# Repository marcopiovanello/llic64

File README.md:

Yet-Another-ControlPort-Converter for the Commodore C64

WIP!!

I'm developing yet another converter for Atari joystick based systems to USB.

What's different from other solutions?

Basically it's externally powered, which means that you can plug virtually anything and not think about drawing too much power from the system (e.g. the 100mA limit of the C64)

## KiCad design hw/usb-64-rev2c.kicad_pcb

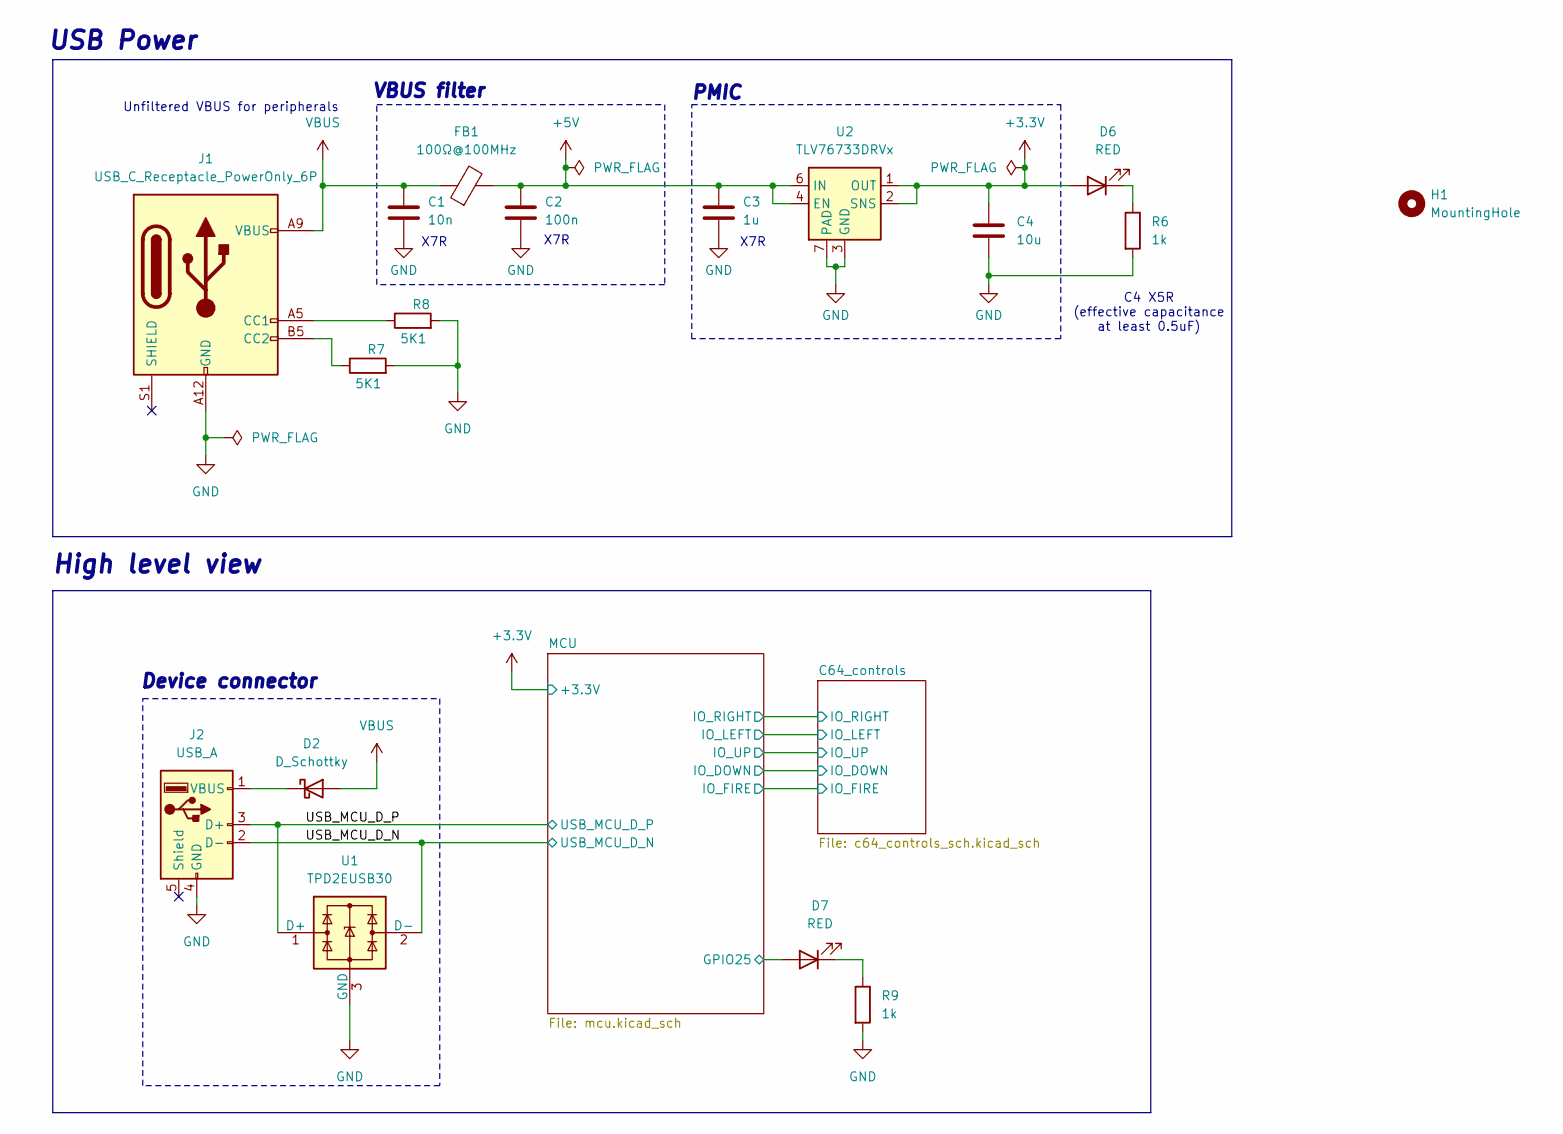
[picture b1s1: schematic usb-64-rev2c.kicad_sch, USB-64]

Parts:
C1: 10n; C_0402_1005Metric; LCSC Part # C15195
C2: 100n; C_0603_1608Metric; LCSC Part # C14663
C3: 1u; C_0603_1608Metric; LCSC Part # C15849
C4: 10u; C_0805_2012Metric; LCSC Part # C440198
D2: D_Schottky; D_SOD-323; LCSC Part # C191023
D6, D7: RED; LED_0603_1608Metric; LCSC Part # C2286
FB1: 100Ω@100MHz; L_0805_2012Metric; LCSC Part # C1015
H1: MountingHole; MountingHole_2.2mm_M2
J1: USB_C_Receptacle_PowerOnly_6P; USB_C_Receptacle_GCT_USB4125-xx-x_6P_TopMnt_Horizontal; LCSC Part # C456012
J2: USB_A; CONN_UJ2-AH-SMT_CUD
R6, R9: 1k; R_0402_1005Metric; LCSC Part # C11702
R7, R8: 5K1; R_0402_1005Metric
U1: TPD2EUSB30; Texas_DRT-3; LCSC Part # C97502
U2: TLV76733DRVx; WSON-6-1EP_2x2mm_P0.65mm_EP1x1.6mm_ThermalVias; LCSC Part # C2848334

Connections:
+3.3V: C4.1, D6.2 (A), U2.1 (OUT), U2.2 (SNS); also elsewhere on the board
+5V: C2.1, C3.1, FB1.2, U2.4 (EN), U2.6 (IN); also elsewhere on the board
/MCU/GPIO25: D7.2 (A); also elsewhere on the board
/USB_MCU_D_N: J2.2 (D-), U1.2 (D-); also elsewhere on the board
/USB_MCU_D_P: J2.3 (D+), U1.1 (D+); also elsewhere on the board
GND: C1.2, C2.2, C3.2, C4.2, J1.A12 (GND), J1.B12 (GND), J2.4 (GND), R6.2, R7.2, R8.2, R9.2, U1.3 (GND), U2.3 (GND), U2.5 (GND), U2.7 (PAD); also elsewhere on the board
unnamed: D2.1 (K), J2.1 (VBUS)
unnamed: D6.1 (K), R6.1
unnamed: D7.1 (K), R9.1
unnamed: J1.A5 (CC1), R8.1
unnamed: J1.B5 (CC2), R7.1
VBUS: C1.1, D2.2 (A), FB1.1, J1.A9 (VBUS), J1.B9 (VBUS)

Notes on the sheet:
PMIC
X7R
USB Power
X7R
High level view
Unfiltered VBUS for peripherals
C4 X5R (effective capacitance at least 0.5uF)
Device connector
VBUS filter

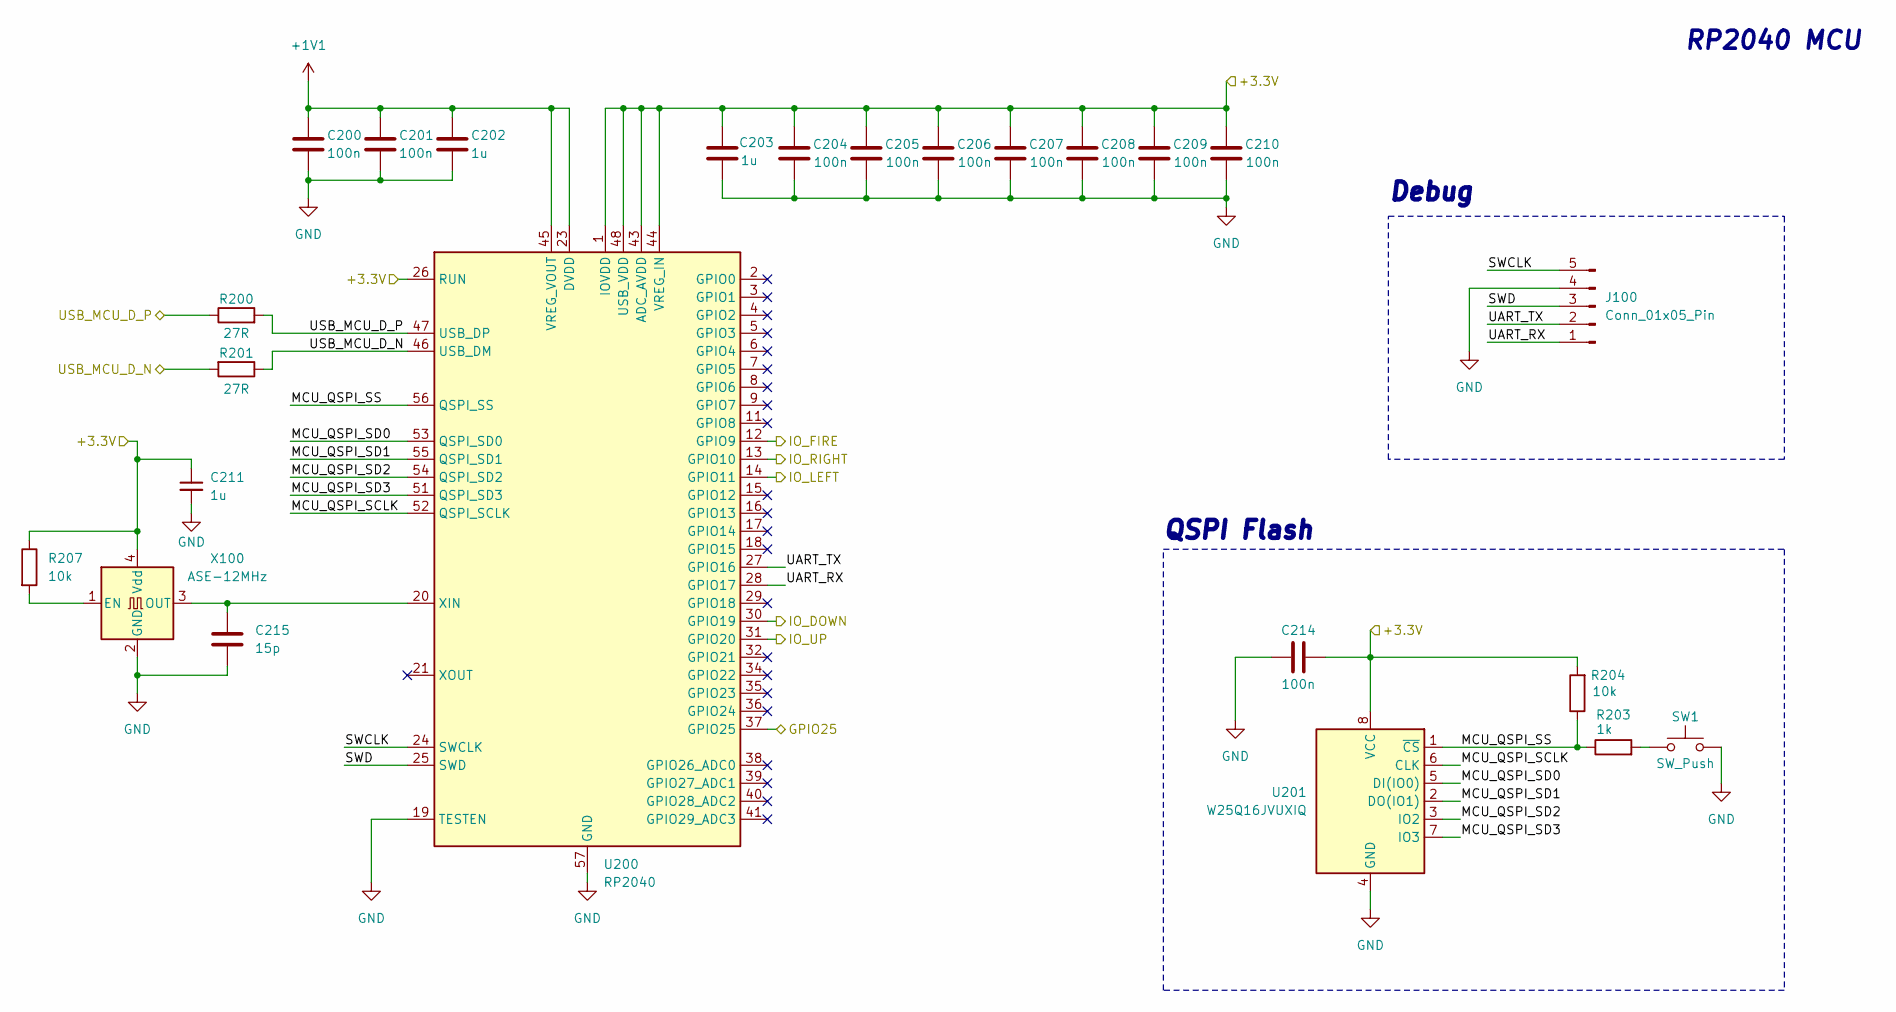
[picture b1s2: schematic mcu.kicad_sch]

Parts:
C200, C201, C204, C205, C206, C207, C208, C209, C210, C214: 100n; C_0402_1005Metric; LCSC Part # C1525
C202, C203, C211: 1u; C_0402_1005Metric; LCSC Part # C52923
C215: 15p; C_0402_1005Metric
J100: Conn_01x05_Pin; PinHeader_1x05_P2.54mm_Vertical
R200, R201: 27R; R_0402_1005Metric; LCSC Part # C25092
R203: 1k; R_0402_1005Metric; LCSC Part # C11702
R204, R207: 10k; R_0402_1005Metric
SW1: SW_Push; SW_SPST_B3U-1000P; LCSC Part # C498294
U200: RP2040; QFN-56-1EP_7x7mm_P0.4mm_EP3.2x3.2mm_ThermalVias
U201: W25Q16JVUXIQ; Winbond_USON-8-1EP_3x2mm_P0.5mm_EP0.2x1.6mm; LCSC Part # C2843335
X100: ASE-12MHz; Crystal_SMD_2016-4Pin_2.0x1.6mm; LCSC Part # C669076

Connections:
+1V1: C200.1, C201.1, C202.1, U200.23 (DVDD), U200.45 (VREG_VOUT), U200.50 (DVDD)
+3.3V: C203.1, C204.1, C205.1, C206.1, C207.1, C208.1, C209.1, C210.1, C211.1, C214.2, R204.2, R207.1, U200.1 (IOVDD), U200.10 (IOVDD), U200.22 (IOVDD), U200.26 (RUN), U200.33 (IOVDD), U200.42 (IOVDD), U200.43 (ADC_AVDD), U200.44 (VREG_IN), U200.48 (USB_VDD), U200.49 (IOVDD), U201.8 (VCC), X100.4 (Vdd); also elsewhere on the board
/C64_controls/IO_DOWN: U200.30 (GPIO19); also elsewhere on the board
/C64_controls/IO_FIRE: U200.12 (GPIO9); also elsewhere on the board
/C64_controls/IO_LEFT: U200.14 (GPIO11); also elsewhere on the board
/C64_controls/IO_RIGHT: U200.13 (GPIO10); also elsewhere on the board
/C64_controls/IO_UP: U200.31 (GPIO20); also elsewhere on the board
/MCU/GPIO25: U200.37 (GPIO25); also elsewhere on the board
/MCU/MCU_QSPI_SCLK: U200.52 (QSPI_SCLK), U201.6 (CLK)
/MCU/MCU_QSPI_SD0: U200.53 (QSPI_SD0), U201.5 (DI(IO0))
/MCU/MCU_QSPI_SD1: U200.55 (QSPI_SD1), U201.2 (DO(IO1))
/MCU/MCU_QSPI_SD2: U200.54 (QSPI_SD2), U201.3 (IO2)
/MCU/MCU_QSPI_SD3: U200.51 (QSPI_SD3), U201.7 (IO3)
/MCU/MCU_QSPI_SS: R203.1, R204.1, U200.56 (QSPI_SS), U201.1 (~CS)
/MCU/SWCLK: J100.5, U200.24 (SWCLK)
/MCU/SWD: J100.3, U200.25 (SWD)
/MCU/UART_RX: J100.1, U200.28 (GPIO17)
/MCU/UART_TX: J100.2, U200.27 (GPIO16)
/USB_MCU_D_N: R201.1, R201.2, U200.46 (USB_DM); also elsewhere on the board
/USB_MCU_D_P: R200.1, R200.2, U200.47 (USB_DP); also elsewhere on the board
GND: C200.2, C201.2, C202.2, C203.2, C204.2, C205.2, C206.2, C207.2, C208.2, C209.2, C210.2, C211.2, C214.1, C215.2, J100.4, SW1.2, U200.19 (TESTEN), U200.57 (GND), U201.4 (GND), X100.2 (GND); also elsewhere on the board
unnamed: R203.2, SW1.1
unnamed: C215.1, U200.20 (XIN), X100.3 (OUT)
unnamed: R207.2, X100.1 (EN)

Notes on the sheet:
Debug
RP2040 MCU
QSPI Flash

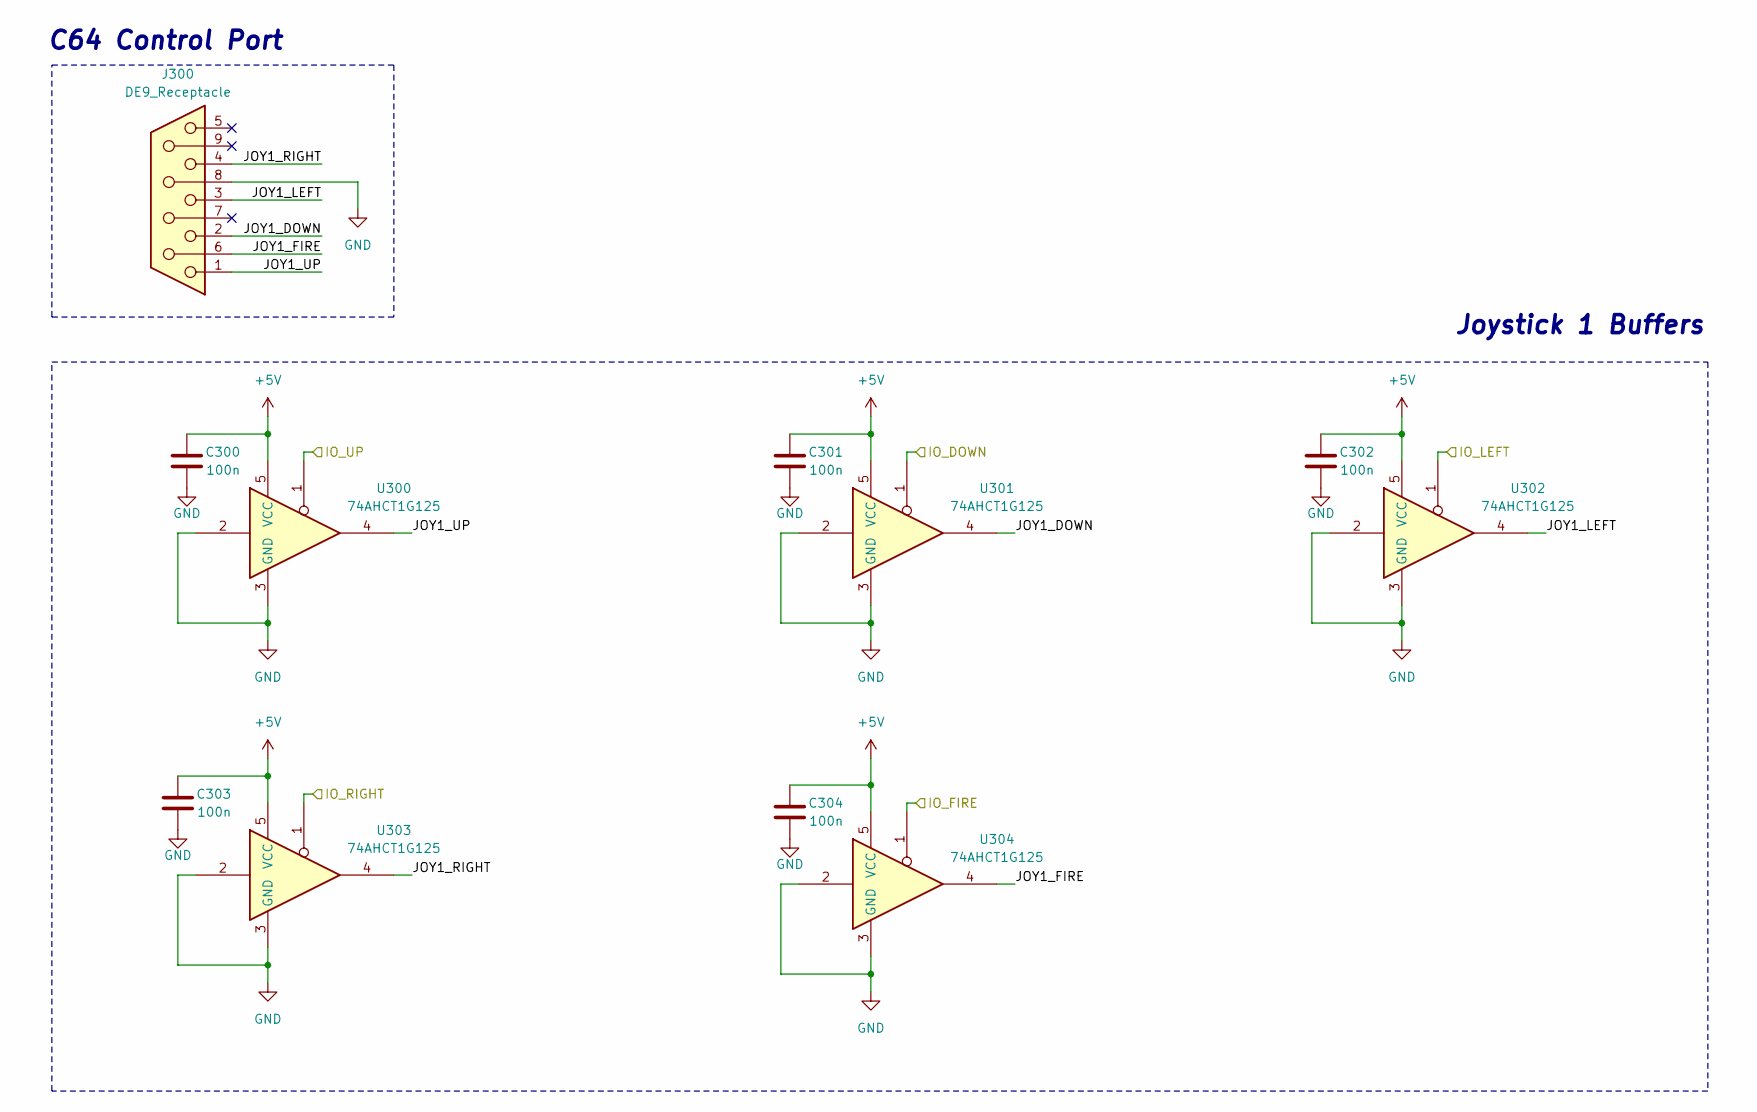
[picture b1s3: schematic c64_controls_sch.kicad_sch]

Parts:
C300, C301, C302, C303, C304: 100n; C_0402_1005Metric; LCSC Part # C1525
J300: DE9_Receptacle; DSUB-9_Female_EdgeMount_P2.77mm
U300, U301, U302, U303, U304: 74AHCT1G125; SOT-353_SC-70-5

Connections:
+5V: C300.1, C301.1, C302.1, C303.1, C304.1, U300.5 (VCC), U301.5 (VCC), U302.5 (VCC), U303.5 (VCC), U304.5 (VCC); also elsewhere on the board
/C64_controls/IO_DOWN: U301.1; also elsewhere on the board
/C64_controls/IO_FIRE: U304.1; also elsewhere on the board
/C64_controls/IO_LEFT: U302.1; also elsewhere on the board
/C64_controls/IO_RIGHT: U303.1; also elsewhere on the board
/C64_controls/IO_UP: U300.1; also elsewhere on the board
/C64_controls/JOY1_DOWN: J300.2, U301.4
/C64_controls/JOY1_FIRE: J300.6, U304.4
/C64_controls/JOY1_LEFT: J300.3, U302.4
/C64_controls/JOY1_RIGHT: J300.4, U303.4
/C64_controls/JOY1_UP: J300.1, U300.4
GND: C300.2, C301.2, C302.2, C303.2, C304.2, J300.8, U300.2, U300.3 (GND), U301.2, U301.3 (GND), U302.2, U302.3 (GND), U303.2, U303.3 (GND), U304.2, U304.3 (GND); also elsewhere on the board

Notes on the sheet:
C64 Control Port
Joystick 1 Buffers

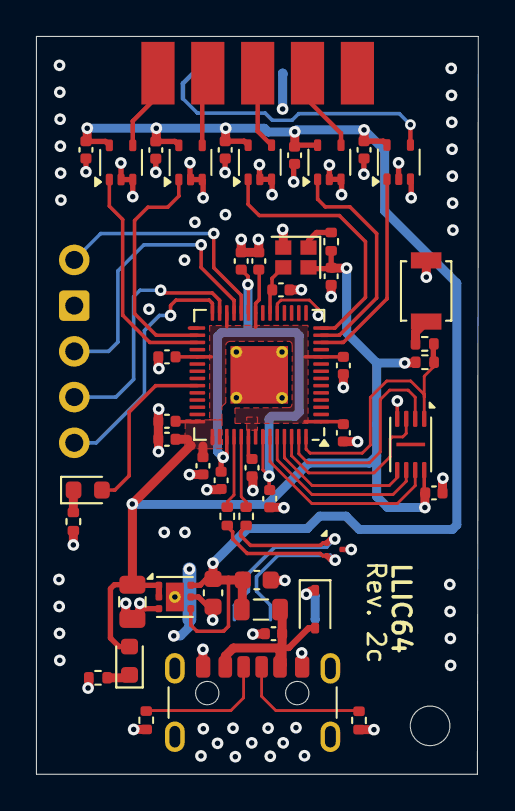
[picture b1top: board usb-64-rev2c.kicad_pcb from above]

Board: 4 copper layers, 24.5 x 41.0 mm, 52 parts (1 on the bottom side), 36 nets.

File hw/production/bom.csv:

Designator,Footprint,Quantity,Value,LCSC Part #
C1,0402,1,10n,C15195
C2,0603,1,100n,C14663
"C200, C201, C204, C205, C206, C207, C208, C209, C210, C214, C300, C301, C302, C303, C304",0402,15,100n,C1525
"C202, C203, C211",0402,3,1u,C52923
C215,0402,1,15p,C1548
C3,0603,1,1u,C15849
C4,0805,1,10u,C440198
D2,D_SOD-323,1,D_Schottky,C191023
"D6, D7",0603,2,RED,C2286
FB1,0805,1,100Ω@100MHz,C1015
J1,USB_C_Receptacle_GCT_USB4125-xx-x_6P_TopMnt_Horizontal,1,USB_C_Receptacle_PowerOnly_6P,C456012
J100,PinHeader_1x05_P2.54mm_Vertical,1,Conn_01x05_Pin,
J2,CONN_UJ2-AH-SMT_CUD,1,USB_A,
J300,DSUB-9_Female_EdgeMount_P2.77mm,1,DE9_Receptacle,
"R200, R201",0402,2,27R,C25092
"R203, R6, R9",0402,3,1k,C11702
"R204, R207",0402,2,10k,
"R7, R8",0402,2,5K1,
SW1,SW_SPST_B3U-1000P,1,SW_Push,C498294
U1,Texas_DRT-3,1,TPD2EUSB30,C97502
U2,WSON-6-1EP_2x2mm_P0.65mm_EP1x1.6mm_ThermalVias,1,TLV76733DRVx,C2848334
U200,QFN-56-1EP_7x7mm_P0.4mm_EP3.2x3.2mm_ThermalVias,1,RP2040,
U201,Winbond_USON-8-1EP_3x2mm_P0.5mm_EP0.2x1.6mm,1,W25Q16JVUXIQ,C2843335
"U300, U301, U302, U303, U304",SOT-353_SC-70-5,5,74AHCT1G125,
X100,Crystal_SMD_2016-4Pin_2.0x1.6mm,1,ASE-12MHz,C669076

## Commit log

2025-01-05 changed pcb specs
2025-01-05 rerouted
2025-01-06 pre production
2025-01-11 1p version
2025-01-11 added 15pf load capacitor for oscillator
2025-01-16 pre production review
2025-01-24 production
2025-01-24 code rafactoring
2025-01-26 move to c++
2025-01-28 keyboard working with NKRO
2025-01-31 code refactoring
2025-02-03 custom hid report + code refactoring
2025-07-05 b for jump
